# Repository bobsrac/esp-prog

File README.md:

# esp-prog

esp32 programmer - USBC to custom DF13-7 connector

This is from the circuit on the [ESP32-C6-DevKitC-1](https://docs.espressif.com/projects/esp-dev-kits/en/latest/esp32c6/esp32-c6-devkitc-1/user_guide.html#hardware-reference)
board from Espressif.  It includes the USB-UART, BJT translators for reset and
boot mode, and a 3.3V LDO.

* Full kicad sources included
* Tested by flashing ESP32-C6-WROOM-1-N8 module using 

## images

## PCA BOM

DigiKey buy list for the PCA (was $11.66 at time of writing) - NOTE: this
is for PCA only.  No target or PC (USB-C) cable parts included:
[http://www.digikey.com/en/mylists/list/WV3N0IXJLB](http://www.digikey.com/en/mylists/list/WV3N0IXJLB)

## PC Cable

The CP2102N is a USB 2.0 full-speed (12 Mbit/s) device, so any USB-C cable with
data lanes should work.

## Target Cable

DigiKey buy list for cable (was $7.54 at time of writing):
[http://www.digikey.com/en/mylists/list/WWA0BU113L](http://www.digikey.com/en/mylists/list/WWA0BU113L)

DF13-7S-1.25C, qty 2:
[http://www.digikey.com/en/products/detail/hirose-electric-co-ltd/DF13-7S-1-25C/241754](http://www.digikey.com/en/products/detail/hirose-electric-co-ltd/DF13-7S-1-25C/241754)

H4BBG-10104-B6, qty 10:
[http://www.digikey.com/en/products/detail/hirose-electric-co-ltd/H4BBG-10104-B6/425553](http://www.digikey.com/en/products/detail/hirose-electric-co-ltd/H4BBG-10104-B6/425553)

Route pin 1 to pin1, and pin 7 to pin 7.  With the pre-crimped wires from
Digi-Key, the cable will want to lay with both connectors facing the same
direction, with a half-twist in the middle.  With the wires all laying flat and
in parallel, one connector will be up while the other is down.

## Template for Target PCA (Board to be programmed)

See [target-template](target-template/).

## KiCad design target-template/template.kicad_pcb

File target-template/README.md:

# esp-prog target-template

PCA design for a board with a ESP32-C6-WROOM-1, power-only USB-C connector,
3.3V LDO, programming connector for the esp-prog, and some testpoints.

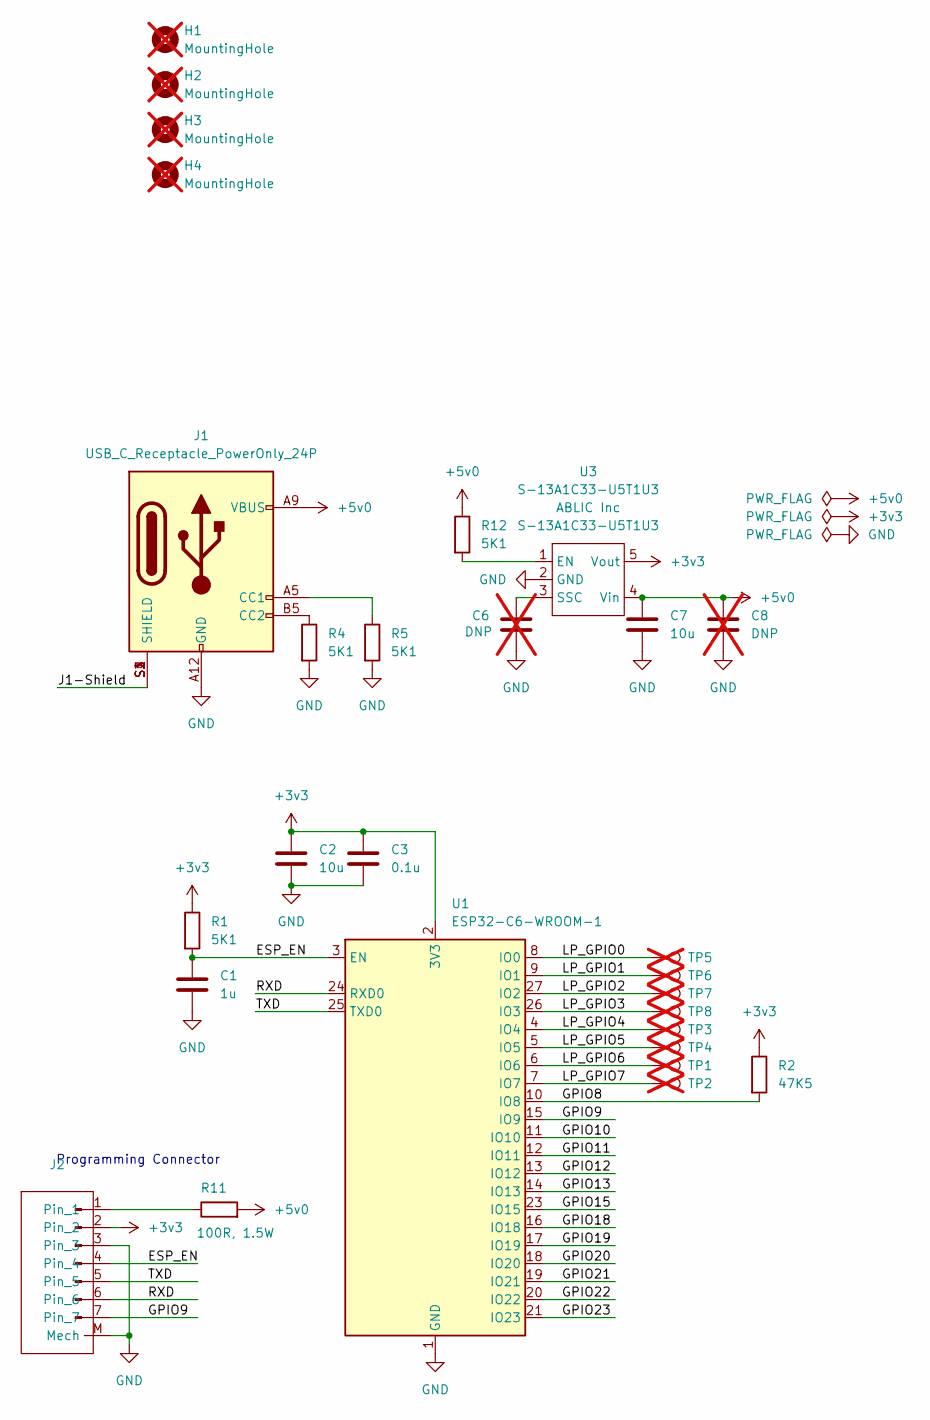
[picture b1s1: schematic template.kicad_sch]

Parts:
C1: 1u; C_0603_1608Metric; Manuf PN CL10B105KP8NNNC
C2, C7: 10u; C_0603_1608Metric; Manuf PN GRM188Z71A106KA73D
C3: 0.1u; C_0603_1608Metric; Manuf PN CC0603KRX7R7BB104
C6: DNP; C_0603_1608Metric; Manuf PN GRT1885C1E103JA02J; not fitted
C8: DNP; C_0603_1608Metric; Manuf PN GRM188Z71A106KA73D; not fitted
H1, H2, H3, H4: MountingHole; MountingHole_2.7mm_M2.5; not fitted
J1: USB_C_Receptacle_PowerOnly_24P; UJC-HP-G-5-SMT-TR; Manuf PN UJC-HP-G-5-SMT-TR
J2: Hirose_DF13-7P-1.25V; Manuf PN DF13-7P-1.25V(76)
R1, R4, R5, R12: 5K1; R_0603_1608Metric; Manuf PN RC0805FR-075K1L
R2: 47K5; R_0603_1608Metric; Manuf PN RC0603FR-0747K5L
R11: 100R, 1.5W; R_0612_1632Metric; Manuf PN LTR18EZPF1000
TP1, TP2, TP3, TP4, TP5, TP6, TP7, TP8: TestPoint; TestPoint_Pad_1.0x1.0mm; not fitted
U1: ESP32-C6-WROOM-1; Manuf PN ESP-32-C6-WROOM-1-N8
U3: S-13A1C33-U5T1U3; SOT-89-5; Manuf PN S-13A1C33-U5T1U3

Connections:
+3v3: C2.1, C3.1, J2.2, R1.1, R2.1, U1.2 (3V3), U3.5 (Vout)
+5v0: C7.1, C8.1, J1.A4 (VBUS), J1.A9 (VBUS), J1.B4 (VBUS), J1.B9 (VBUS), R11.2, R12.1, U3.4 (Vin)
/ESP_EN: C1.1, J2.4, R1.2, U1.3 (EN)
/GPIO8: R2.2, U1.10 (IO8)
/GPIO9: J2.7, U1.15 (IO9)
/GPIO10: U1.11 (IO10)
/GPIO11: U1.12 (IO11)
/GPIO12: U1.13 (IO12)
/GPIO13: U1.14 (IO13)
/GPIO15: U1.23 (IO15)
/GPIO18: U1.16 (IO18)
/GPIO19: U1.17 (IO19)
/GPIO20: U1.18 (IO20)
/GPIO21: U1.19 (IO21)
/GPIO22: U1.20 (IO22)
/GPIO23: U1.21 (IO23)
/J1-Shield: J1.S1 (SHIELD), J1.S2 (SHIELD), J1.S3 (SHIELD), J1.S4 (SHIELD)
/LP_GPIO0: TP5.1, U1.8 (IO0)
/LP_GPIO1: TP6.1, U1.9 (IO1)
/LP_GPIO2: TP7.1, U1.27 (IO2)
/LP_GPIO3: TP8.1, U1.26 (IO3)
/LP_GPIO4: TP3.1, U1.4 (IO4)
/LP_GPIO5: TP4.1, U1.5 (IO5)
/LP_GPIO6: TP1.1, U1.6 (IO6)
/LP_GPIO7: TP2.1, U1.7 (IO7)
/RXD: J2.6, U1.24 (RXD0)
/TXD: J2.5, U1.25 (TXD0)
GND: C1.2, C2.2, C3.2, C6.2, C7.2, C8.2, J1.A1 (GND), J1.A12 (GND), J1.B1 (GND), J1.B12 (GND), J2.3, J2.M (Mech), R4.2, R5.2, U1.1 (GND), U1.28 (GND), U1.29 (GND), U3.2 (GND)
unnamed: J1.A5 (CC1), R5.1
unnamed: J1.B5 (CC2), R4.1
unnamed: J2.1, R11.1
unnamed: R12.2, U3.1 (EN)
unnamed: C6.1, U3.3 (SSC)

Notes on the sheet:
Programming Connector

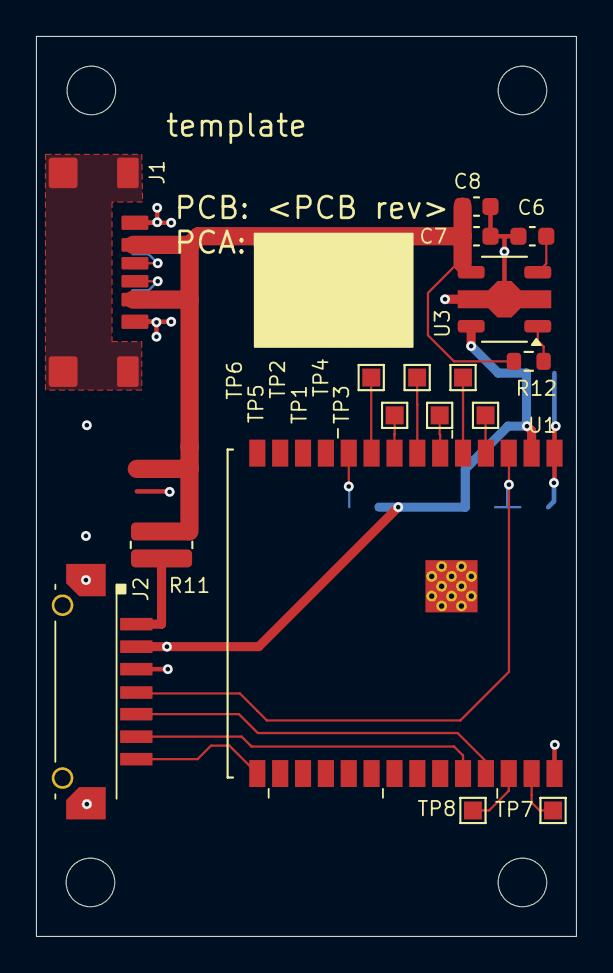
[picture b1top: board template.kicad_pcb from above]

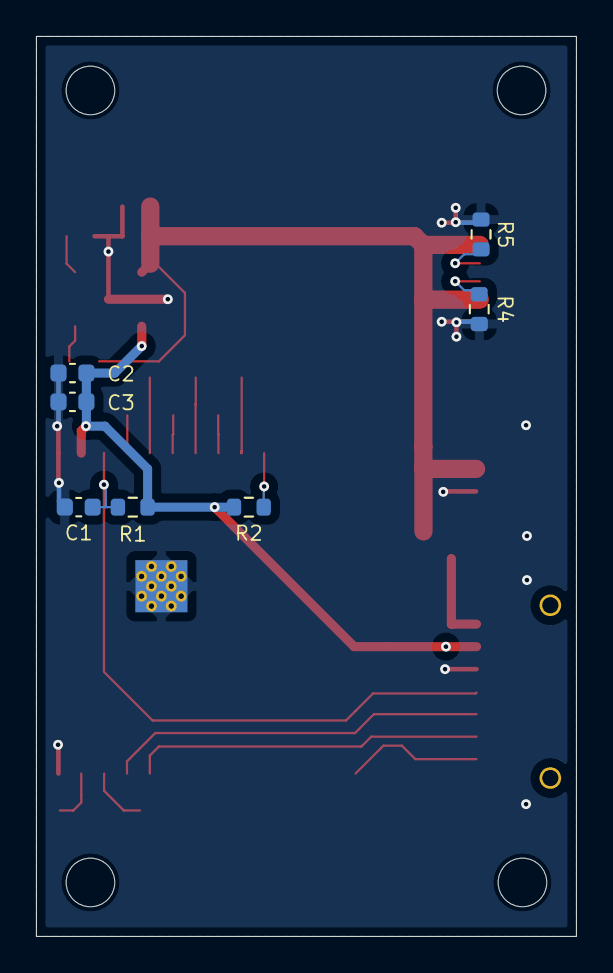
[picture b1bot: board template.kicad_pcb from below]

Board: 2 copper layers, 30.0 x 50.0 mm, 28 parts (7 on the bottom side), 22 nets.

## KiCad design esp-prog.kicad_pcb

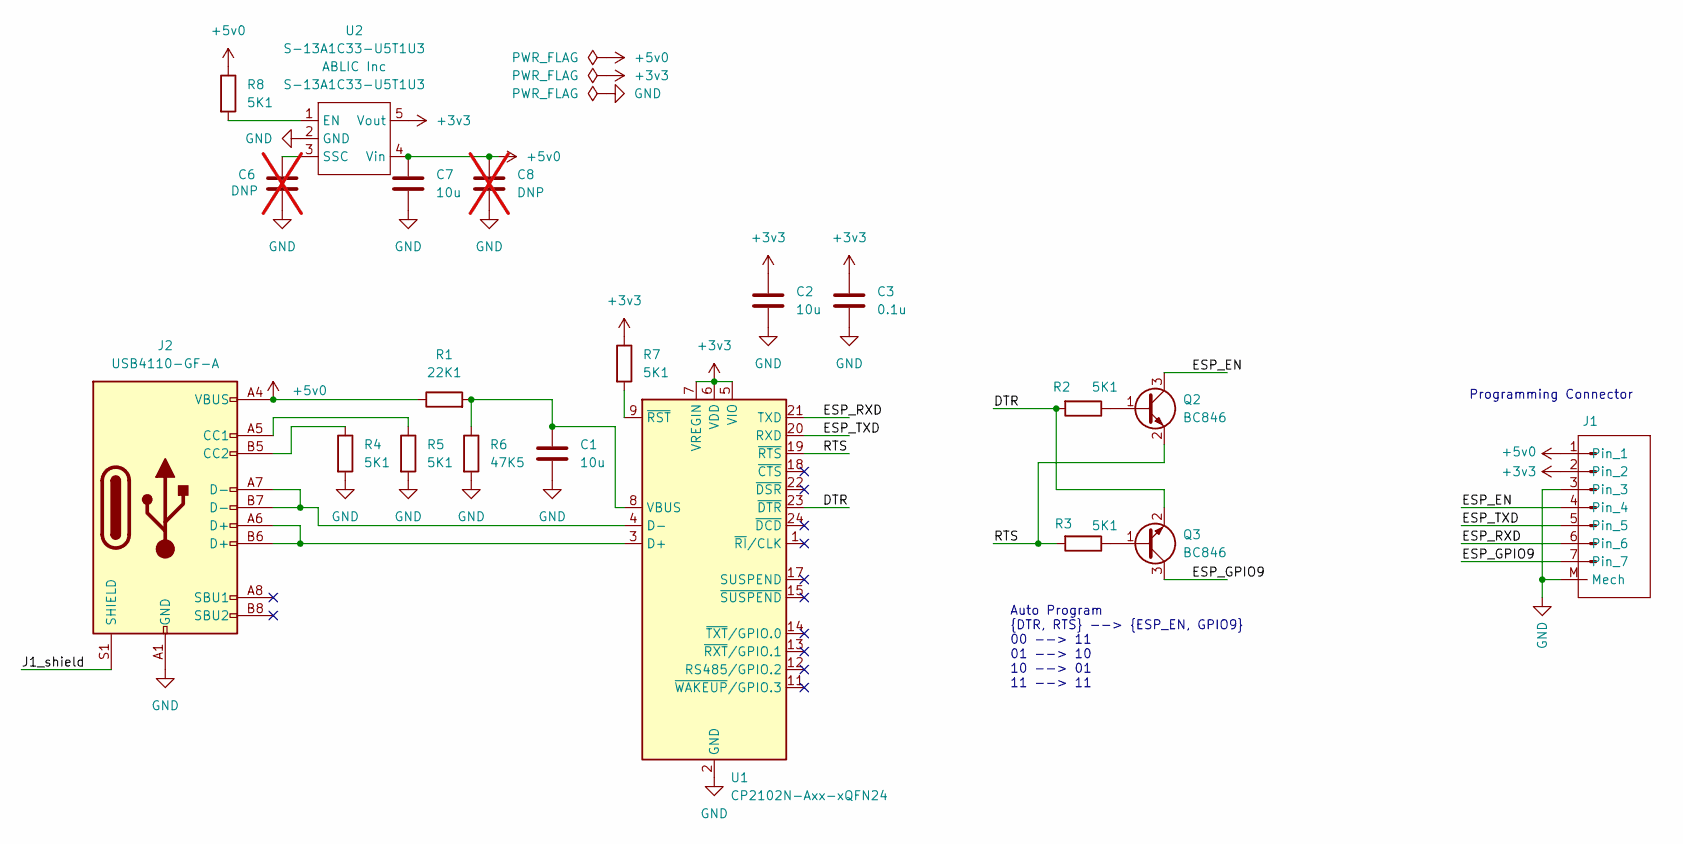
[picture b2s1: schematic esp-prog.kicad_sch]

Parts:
C1, C2, C7: 10u; C_0603_1608Metric; Manuf PN GRM188Z71A106KA73D
C3: 0.1u; C_0603_1608Metric; Manuf PN CC0603KRX7R7BB104
C6: DNP; C_0603_1608Metric; Manuf PN GRT1885C1E103JA02J; not fitted
C8: DNP; C_0603_1608Metric; Manuf PN GRM188Z71A106KA73D; not fitted
J1: Hirose_DF13-7P-1.25V; Manuf PN DF13-7P-1.25V(76)
J2: USB4110-GF-A; Manuf PN USB4110-GF-A
Q2, Q3: BC846; SOT-23; Manuf PN BC846,215
R1: 22K1; R_0603_1608Metric; Manuf PN RC0603FR-0722K1L
R2, R3, R4, R5, R7, R8: 5K1; R_0603_1608Metric; Manuf PN RC0603FR-075K1L
R6: 47K5; R_0603_1608Metric; Manuf PN RC0603FR-0747K5L
U1: CP2102N-Axx-xQFN24; QFN-24-1EP_4x4mm_P0.5mm_EP2.6x2.6mm; Manuf PN CP2102N-A02-GQFN24R
U2: S-13A1C33-U5T1U3; SOT-89-5; Manuf PN S-13A1C33-U5T1U3

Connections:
+3v3: C2.1, C3.1, J1.2, R7.1, U1.5 (VIO), U1.6 (VDD), U1.7 (VREGIN), U2.5 (Vout)
+5v0: C7.1, C8.1, J1.1, J2.A4 (VBUS), J2.A9 (VBUS), J2.B4 (VBUS), J2.B9 (VBUS), R1.1, R8.1, U2.4 (Vin)
/DTR: Q3.2 (E), R2.2, U1.23 (~DTR)
/ESP_EN: J1.4, Q2.3 (C)
/ESP_GPIO9: J1.7, Q3.3 (C)
/ESP_RXD: J1.6, U1.21 (TXD)
/ESP_TXD: J1.5, U1.20 (RXD)
/J1_shield: J2.S1 (SHIELD)
/RTS: Q2.2 (E), R3.2, U1.19 (~RTS)
GND: C1.2, C2.2, C3.2, C6.2, C7.2, C8.2, J1.3, J1.M (Mech), J2.A1 (GND), J2.A12 (GND), J2.B1 (GND), J2.B12 (GND), R4.2, R5.2, R6.2, U1.2 (GND), U1.25 (GND), U2.2 (GND)
unnamed: J2.A5 (CC1), R5.1
unnamed: J2.B5 (CC2), R4.1
unnamed: Q2.1 (B), R2.1
unnamed: Q3.1 (B), R3.1
unnamed: J2.A6 (D+), J2.B6 (D+), U1.3 (D+)
unnamed: J2.A7 (D-), J2.B7 (D-), U1.4 (D-)
unnamed: C1.1, R1.2, R6.1, U1.8 (VBUS)
unnamed: R7.2, U1.9 (~RST)
unnamed: R8.2, U2.1 (EN)
unnamed: C6.1, U2.3 (SSC)

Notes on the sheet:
Auto Program {DTR, RTS} --> {ESP_EN, GPIO9} 00 --> 11 01 --> 10 10 --> 01 11 --> 11
Programming Connector

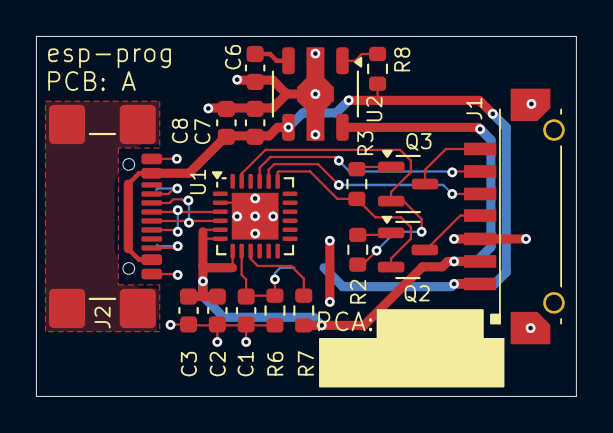
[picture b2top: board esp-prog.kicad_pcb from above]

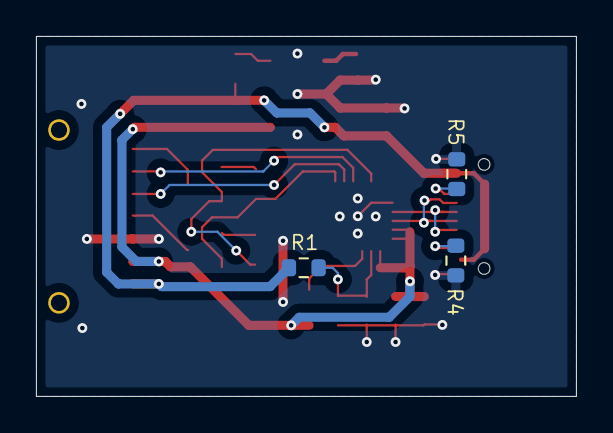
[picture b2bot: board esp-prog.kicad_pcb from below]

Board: 2 copper layers, 30.0 x 20.0 mm, 20 parts (3 on the bottom side), 19 nets.

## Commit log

2024-07-30 revA as-built
2024-07-30 added template for a target PCA
